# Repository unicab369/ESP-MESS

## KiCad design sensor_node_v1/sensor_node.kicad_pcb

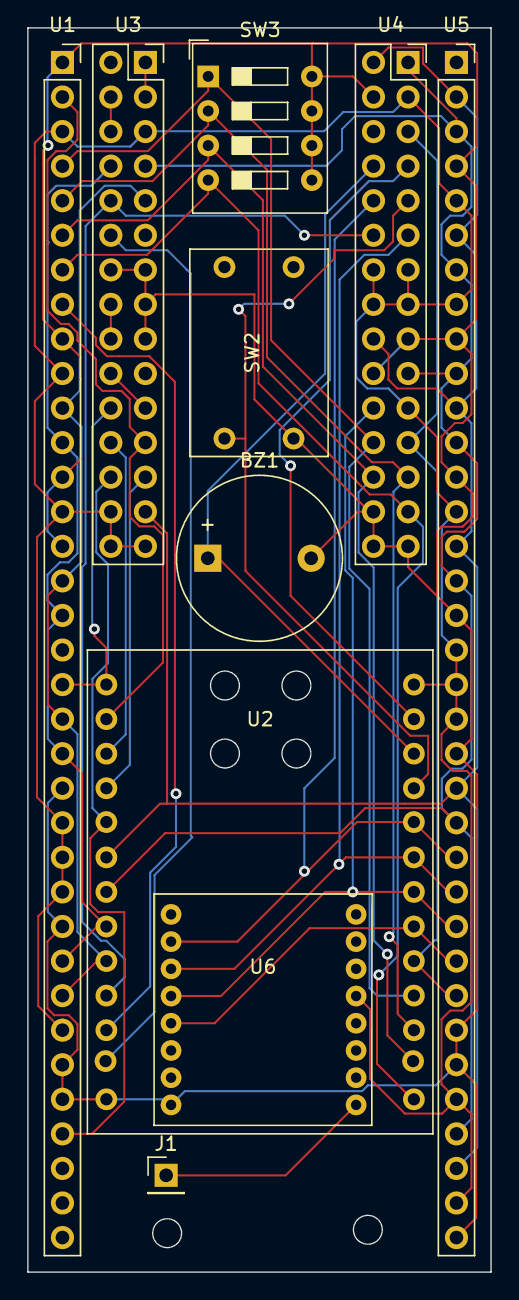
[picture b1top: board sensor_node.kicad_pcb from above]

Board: 2 copper layers, 34.0 x 91.4 mm, 10 parts (0 on the bottom side), 31 nets.

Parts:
BZ1: Buzzer; Buzzer_12x9.5RM7.6
J1: Conn_01x01_Female; PinHeader_1x01_P2.54mm_Vertical
SW2: SW_Push; MyButton
SW3: SW_DIP_x04; SW_DIP_SPSTx04_Slide_9.78x12.34mm_W7.62mm_P2.54mm
U1: ARR_A0; PinSocket_1x35_P2.54mm_Vertical
U2: Lolin32_Base; Lolin32_Lite
U3: ARR_A1; PinSocket_2x15_P2.54mm_Vertical
U4: ARR_B1; PinSocket_2x15_P2.54mm_Vertical
U5: ARR_B0; PinSocket_1x35_P2.54mm_Vertical
U6: RFM69

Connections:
+3V3: U1.3 (3.3V), U1.10 (3.3V), U1.14 (3.3V), U1.23 (3.3V), U1.24 (_3.3V), U1.25 (_3.3V), U1.29 (3.3V), U2.14 (3.3V), U3.5 (3.3V), U3.28 (3.3V), U3.29 (3.3V), U3.30 (3.3V), U4.3 (3.3V), U4.13 (3.3V), U4.14 (3.3V), U4.15 (3.3V), U4.16 (_VCC), U4.21 (3.3V), U5.5 (3.3V), U5.8 (3.3V), U5.14 (ADDR), U5.18 (3.3V), U5.19 (_3.3V), U5.20 (3.3V), U5.31 (3.3V), U5.34 (_3.3V), U6.12 (3.3V)
/#A0: SW3.3, U1.6 (#A0), U2.25 (15), U4.26 (15)
/#CS: U1.8 (#CS), U2.11 (14)
/#RST: SW3.4, U1.7 (#RST), U2.26 (13), U4.27 (13)
/#SCK: SW3.1, U1.4 (#SCK), U2.23 (0), U4.24 (0)
/#SDA: SW3.2, U1.5 (#SDA), U2.24 (2), U4.25 (2)
/BTN2: SW2.1, U2.17 (23), U4.9 (23)
/BUZ1: BZ1.1 (-), U2.16 (19), U4.8 (19)
/CS: U2.21 (16), U5.27 (RST), U6.5 (CS)
/DIO: U2.22 (4), U4.5 (23), U4.23 (4), U5.28 (DIO)
/EN: U2.3 (EN), U3.24 (EN)
/EN2: U3.1 (_EN2), U3.3 (EN2)
/IO_2: U3.16 (_IO_2), U3.18 (IO_2)
/IO_3: U3.20 (IO_3), U3.21 (_IO_3)
/LED: U2.15 (22), U4.7 (22)
/MISO: U2.18, U4.10 (18), U5.24 (MISO), U6.2 (MISO)
/MOSI: U2.19 (5), U4.11 (5), U5.25 (MOSI), U6.3 (MOSI)
/PIR0: U1.19 (VP_36), U2.1 (VP_36), U3.22 (VP_36)
/PIR1: U1.2 (VN_39), U2.2 (VN_39), U3.23 (VN_39)
/PIR2: U2.4 (34), U3.25 (34)
/PIR3: U1.32 (35), U2.5 (35), U3.26 (35)
/RST2: U3.4 (RST2), U3.6 (_RST2)
/SCK: U2.20 (7), U4.22 (16), U5.26 (CS), U6.4 (SCK)
/SCL: U1.12 (_SDA), U1.17 (SDA), U1.21 (SCL), U1.27 (SCL), U2.8 (25), U3.8 (25)
/SCL1: U2.7 (33), U3.7 (33), U4.1 (_SCL), U4.19 (SCL), U5.3 (SCL1), U5.7 (SCL1), U5.10 (_SCL1), U5.12 (_GND), U5.16 (SCL1), U5.23 (SDA1), U5.32 (SDA1)
/SDA: U1.11 (_SCL), U1.16 (SCL), U1.20 (SDA), U1.28 (SDA), U2.9 (26), U3.9 (26)
/SDA1: U2.6 (32), U3.27 (32), U4.2 (_SDA), U4.18 (SDA), U5.2 (SDA1), U5.6 (SDA1), U5.11 (_SDA1), U5.15 (SDA1), U5.22 (SCL1), U5.33 (SCL1)
/WS28: U2.12, U3.12
/X_1: U2.10 (27), U3.10 (27), U4.12 (17)
GND: BZ1.2 (+), SW2.2, SW3.5, SW3.6, SW3.7, SW3.8, U1.1 (GND), U1.9 (GND), U1.13 (_GND), U1.15 (GND), U1.22 (GND), U1.26 (_GND), U1.30 (GND), U1.31 (GND), U2.13 (GND), U3.13 (GND), U3.14 (GND), U3.15 (GND), U3.17 (GND), U4.4 (GND), U4.17 (_GND), U4.20 (GND), U4.28 (GND), U4.29 (GND), U4.30 (GND), U5.4 (GND), U5.9 (GND), U5.13 (_3.3V), U5.17 (GND), U5.21 (GND), U5.29 (GND), U5.30 (GND), U5.35 (_GND), U6.8 (GND)
unnamed: J1.1, U6.16 (ANT)
